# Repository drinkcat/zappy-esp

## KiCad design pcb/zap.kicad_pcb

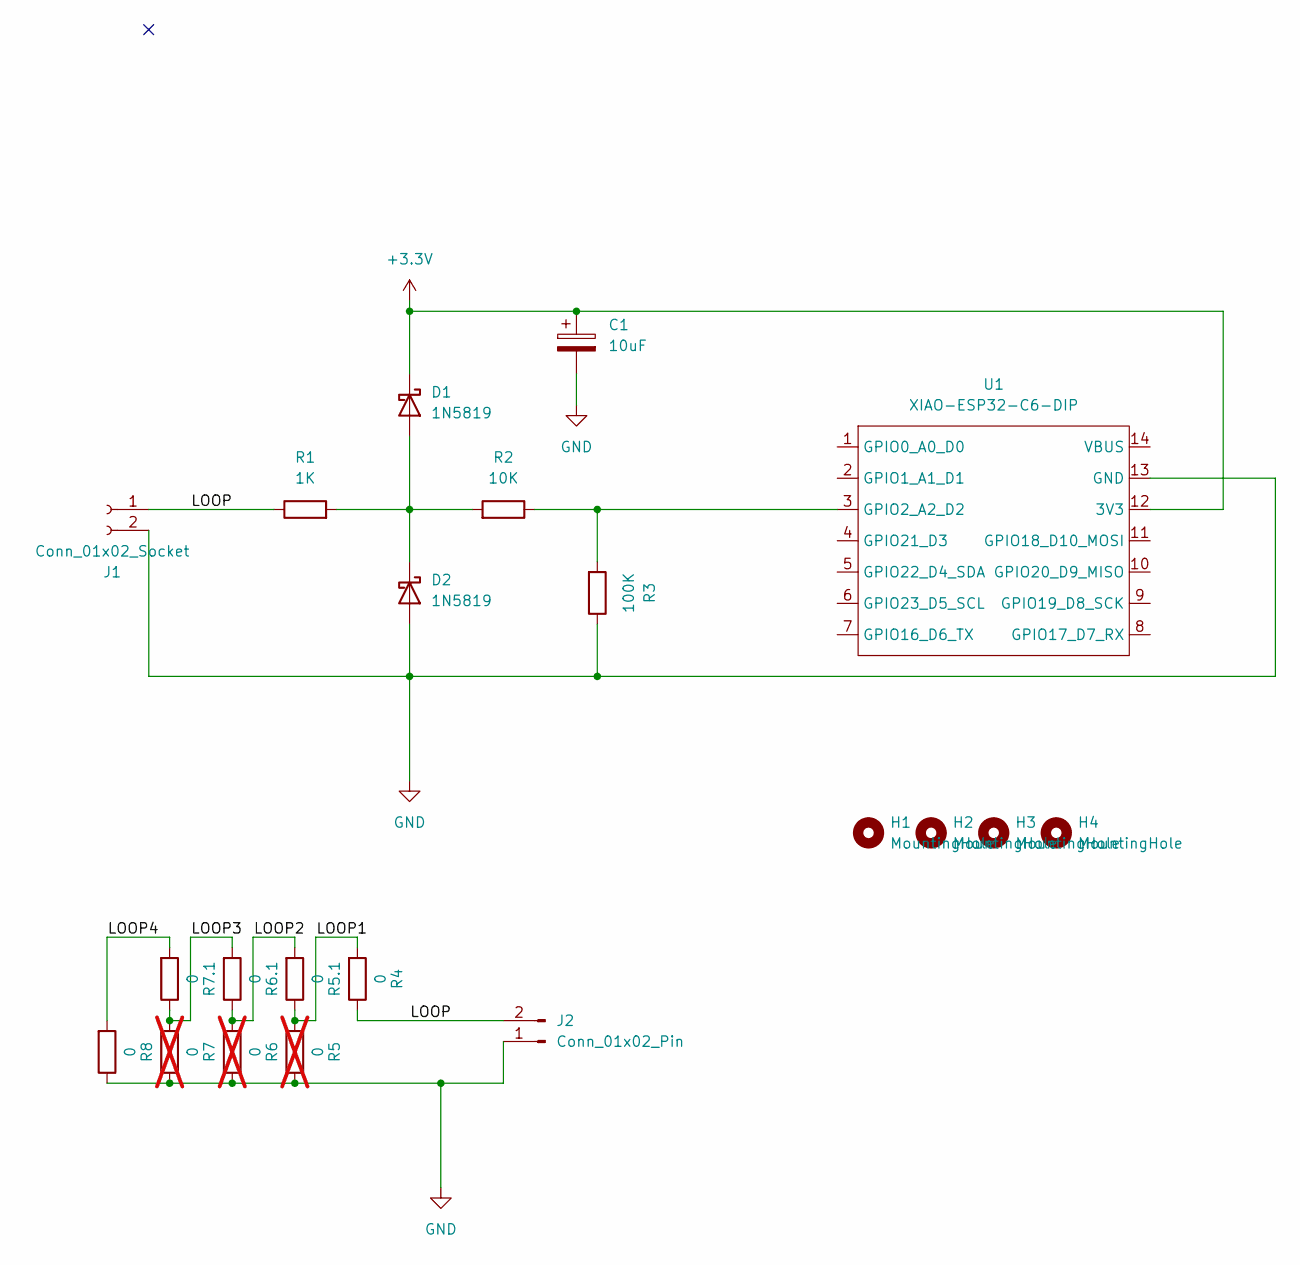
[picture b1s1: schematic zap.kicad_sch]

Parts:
C1: 10uF; C_1206_3216Metric_Pad1.33x1.80mm_HandSolder
D1, D2: 1N5819; D_SOD-323_HandSoldering
H1, H2, H3, H4: MountingHole; ToolingHole_1.152mm
J1: Conn_01x02_Socket; PinHeader_1x02_P2.54mm_Vertical
J2: Conn_01x02_Pin; PinHeader_1x02_P2.54mm_Vertical
R1: 1K; R_1206_3216Metric_Pad1.30x1.75mm_HandSolder
R2: 10K; R_1206_3216Metric_Pad1.30x1.75mm_HandSolder
R3: 100K; R_1206_3216Metric_Pad1.30x1.75mm_HandSolder
R4, R5.1, R6.1, R7.1, R8: 0; R_1206_3216Metric_Pad1.30x1.75mm_HandSolder
R5, R6, R7: 0; R_1206_3216Metric_Pad1.30x1.75mm_HandSolder; not fitted
U1: XIAO-ESP32-C6-DIP; PARTREV 1.3

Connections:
+3.3V: C1.1, D1.1 (K), U1.12 (3V3)
/LOOP: J1.1, J2.2, R1.1, R4.1
/LOOP1: R4.2, R5.2, R5.1.1
/LOOP2: R5.1.2, R6.2, R6.1.1
/LOOP3: R6.1.2, R7.2, R7.1.1
/LOOP4: R7.1.2, R8.2
GND: C1.2, D2.2 (A), J1.2, J2.1, R3.1, R5.1, R6.1, R7.1, R8.1, U1.13 (GND)
unnamed: D1.2 (A), D2.1 (K), R1.2, R2.2
unnamed: R2.1, R3.2, U1.3 (GPIO2_A2_D2)

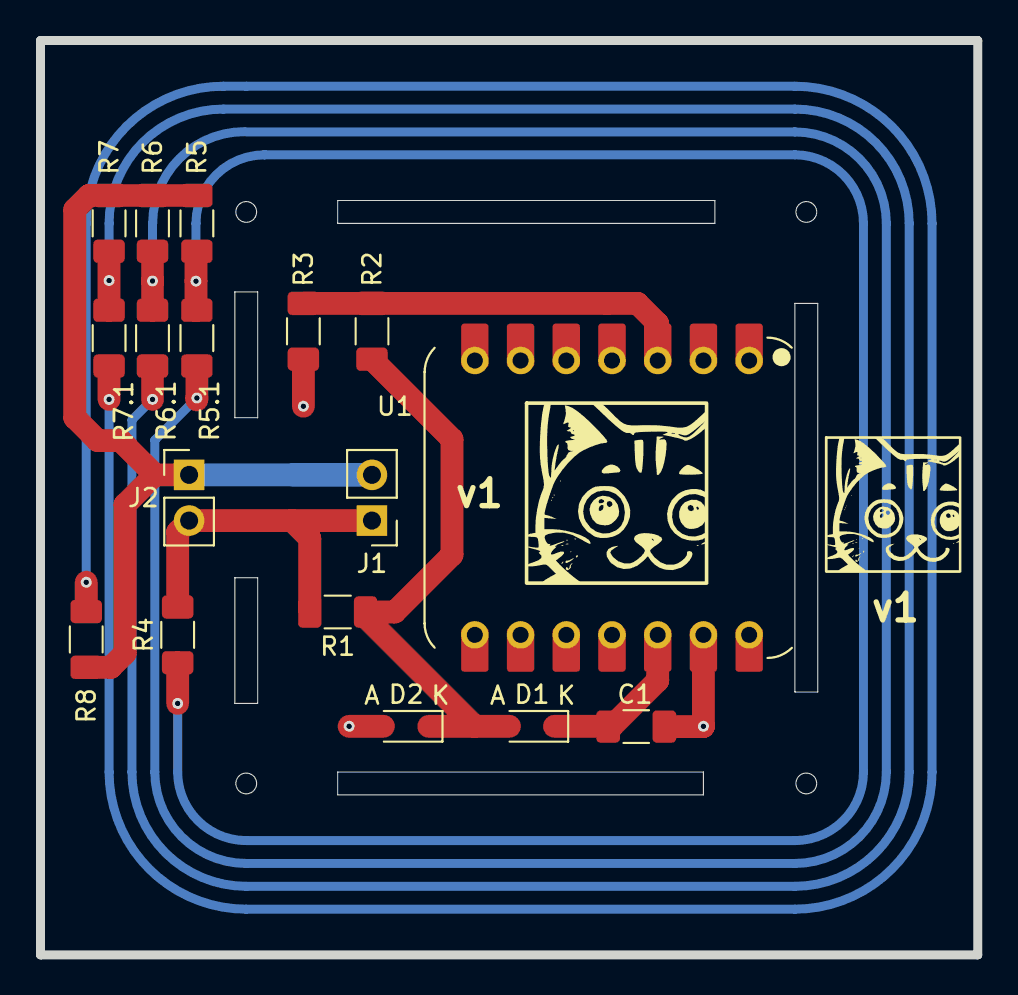
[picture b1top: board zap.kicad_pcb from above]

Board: 2 copper layers, 52.1 x 50.8 mm, 23 parts (0 on the bottom side), 9 nets.

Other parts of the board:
v1, v1#2: LOGO; logo-1cm

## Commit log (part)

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2026-03-22 .cargo/config.toml: Faster flash
2026-03-22 just LED blinking
2026-03-22 Revert "just LED blinking"
    This reverts commit 1df1f02236b0b0bf66d036c430a6994308d5ac60.
2026-03-29 Lots of stuff, I'm lost at this stage
2026-04-05 init: cargo generate esp-rs/esp-idf-template cargo
2026-04-05 .cargo/config.toml: Use esp-idf 6.0 (I like danger)
    Also try to increase flash speed a bit.
2026-04-05 .gitignore: Do not commit src/secrets.rs
2026-04-05 Cargo.toml: Add support for the LED, if needed
    Also embuild from git, not 100% needed.
2026-04-05 esp-generate: init
2026-04-05 Disable clippy::large_stack_frames
2026-04-06 Add board time on boot
2026-04-06 Show first 2 letters of token on boot, for debugging
2026-05-05 Add schematics and PCB
